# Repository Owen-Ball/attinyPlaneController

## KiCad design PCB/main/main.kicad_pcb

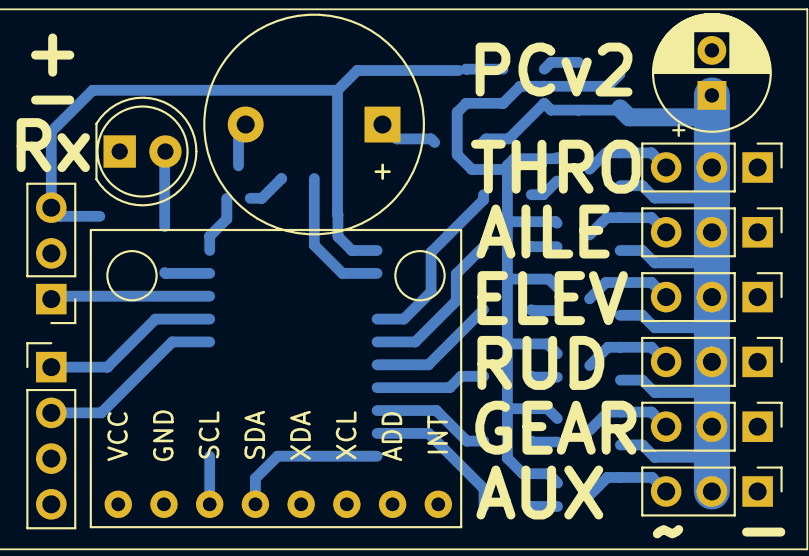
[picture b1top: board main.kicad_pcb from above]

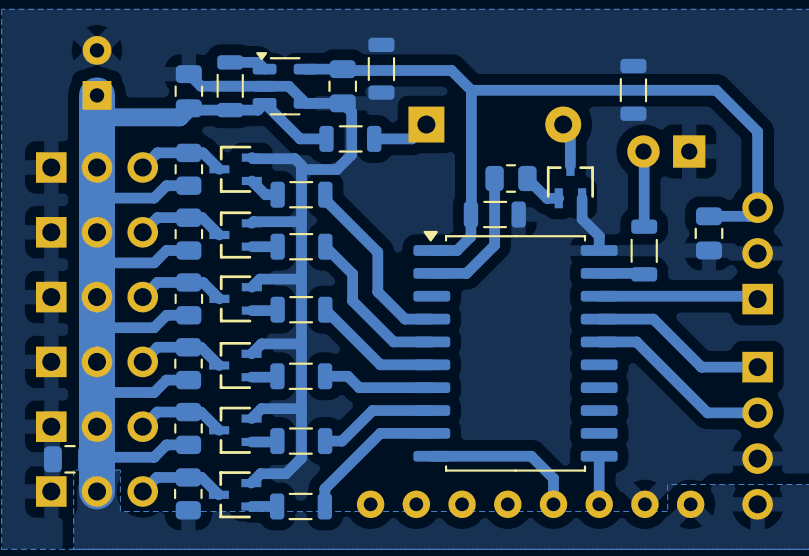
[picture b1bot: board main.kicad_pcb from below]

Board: 2 copper layers, 44 parts (32 on the bottom side), 32 nets.

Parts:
BZ1: Buzzer; Buzzer_12x9.5RM7.6
C1: C; C_0805_Long
C2, C6: 10u; C_0805_2012Metric
C3: 1u; C_0805_2012Metric
C4: 220u; CP_Radial_D6.3mm_P2.50mm
C5: C; C_0805_2012Metric
D1: LED; LED_D5.0mm
J1, J2, J3, J4, J5, J6, J8: Conn_01x03_Pin; PinHeader_1x03_P2.54mm_Vertical
J7: Conn_01x04_Pin; PinHeader_1x04_P2.54mm_Vertical
R1, R4, R6, R8, R10, R12, R13: R_US; R_0805_2012Metric
R2, R3, R5, R7, R9, R11: R_US; C_0805_Long
R14: 470; C_0805_Long
R15, R16, R17, R18: 0; C_0805_Long
U1: ATtiny3226-S; SOIC-20W_7.5x12.8mm_P1.27mm
U2: TPS7A2033PDBVR; SOT-23-5
U3, U4, U5, U6, U7, U8, U9: DMG1012UW-7; SOT_12UW-7_DIO
U10: module_mpu6050

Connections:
+3V3: C1.1, C2.1, C5.1, J8.3, U1.1 (VCC), U2.5 (OUT)
+5V: BZ1.1 (+), C3.1, C4.1, C6.1, J1.2, J2.2, J3.2, J4.2, J5.2, J6.2, J7.4, R1.1, R4.1, R6.1, R8.1, R10.1, R12.1, R15.1, R16.1, R16.2, U2.3 (EN), U10.1 (VCC)
/BUZ: R13.1, U1.2 (PA4)
/DEBUG_TX: J7.1, U1.17 (PA1)
/LED: R14.2, U1.19 (PA3)
/PWM1: J1.3, R1.2, U3.3 (D)
/PWM1_b: R2.1, U1.4 (PA6)
/PWM2: J2.3, R4.2, U4.3 (D)
/PWM2_b: R3.1, U1.5 (PA7)
/PWM3: J3.3, R6.2, U5.3 (D)
/PWM3_b: R5.1, U1.6 (PB5)
/PWM4: J4.3, R8.2, U6.3 (D)
/PWM4_b: R7.1, U1.7 (PB4)
/PWM5: J5.3, R10.2, U7.3 (D)
/PWM5_b: R9.1, U1.8 (PB3)
/PWM6: J6.3, R12.2, U8.3 (D)
/PWM6_b: R11.1, U1.9 (PB2)
/RX: J8.1, U1.18 (PA2)
/SCL: U1.11 (PB0), U10.3 (SCL)
/SDA: U1.10 (PB1), U10.4 (SDA)
/UPDI: J7.2, U1.16 (~RESET/PA0)
GND: C1.2, C2.2, C3.2, C4.2, C5.2, C6.2, D1.1 (K), J1.1, J2.1, J3.1, J4.1, J5.1, J6.1, J7.3, J8.2, R17.1, R17.2, R18.1, R18.2, U1.20 (GND), U2.2 (GND), U2.4 (NC), U3.2 (S), U4.2 (S), U5.2 (S), U6.2 (S), U7.2 (S), U8.2 (S), U9.2 (S), U10.2 (GND)
unnamed: BZ1.2 (-), U9.3 (D)
unnamed: D1.2 (A), R14.1
unnamed: R15.2, U2.1 (IN)
unnamed: R2.2, U3.1 (G)
unnamed: R3.2, U4.1 (G)
unnamed: R5.2, U5.1 (G)
unnamed: R7.2, U6.1 (G)
unnamed: R9.2, U7.1 (G)
unnamed: R11.2, U8.1 (G)
unnamed: R13.2, U9.1 (G)

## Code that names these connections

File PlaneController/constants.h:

#ifndef _CONSTANTS_
#define _CONSTANTS_

enum MODE {FAILSAFE, RATE_MODE, ANGLE_MODE, MANUAL_MODE};
enum SWITCH_MODE {ANGLE_MANUAL, RATE_MANUAL};

#define ELEV_ANGLE  25.0
#define AIL_ANGLE   25.0
#define RUD_RATE    300.0
#define MIN_THROTTLE  20 //out of 255

#define RC_MIN  153.0
#define RC_MAX  870.0

#define SSPIN PIN_PC3
#define BUZ_PIN PIN_PA4
#define BAT_PIN PIN_PB1

#define MOTOR1 PIN_PA6
#define MOTOR2 PIN_PA5
#define MOTOR3 PIN_PA3
#define MOTOR4 PIN_PB0

#define SWITCH_TIME 200000

#define IMU_ADDR  0x68

#define AX_MAX 8280
#define AX_MIN -8140

#endif

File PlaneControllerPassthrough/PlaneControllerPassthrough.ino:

#include <Arduino.h>
#include "PID.h"
#include "Buzzer.h"
#include "RC.h"
#include "IMU.h"
#include "helpers.h"
#include "Motors.h"
#include "FSM.h"
#include "Servo_inverted.h"
//#include <Servo_megaTinyCore.h>

long t;
long loop_time;
long prev_time;

//PID elev(1, .5, .175);
//PID ail(1, .5, .175);
PID elev(.8, .5, .125);
PID ail(.8, .5, .125);
PID rud(2, 0, 0);

Buzzer buzzer(BUZ_PIN);

bool armed = false;

Servo elevator_servo;
Servo aileron_servo;
Servo rudder_servo;
Servo throttle_servo;
Servo aux_servo;
Servo gear_servo;

void setup() {
  Serial1.begin(115200);
  Serial.begin(115200);

  analogReference(INTERNAL2V5);

  initRC(Serial1);
  
  initIMU();
  initFSM(buzzer);

  prev_time = micros();
  
  throttle_servo.attach(PIN_PA6);
  elevator_servo.attach(PIN_PB5);
  aileron_servo.attach(PIN_PA7);
  rudder_servo.attach(PIN_PB4);
  aux_servo.attach(PIN_PC0);
  gear_servo.attach(PIN_PB3);

  delay(3000);

  
}

float limitFloat(float val) {
  if (val > 2000.0) return 2000.0;
  if (val < 1000.0) return 1000.0;
  return val;
}

void loop() {
  t = micros();
  loop_time = t - prev_time;
  prev_time = t;
  runRC(t);
  runFSM(t);
  buzzer.runBuzzer(t);

  runIMU(loop_time);
  //Serial1.print(getThrottle());
  //Serial1.print(" ");
  //Serial1.println(getAileron());
  if (SYSTEM_MODE == FAILSAFE) {
    throttle_servo.writeMicroseconds(1000);
    elevator_servo.writeMicroseconds(1500);
    aileron_servo.writeMicroseconds(1500);
    rudder_servo.writeMicroseconds(1500);
    aux_servo.writeMicroseconds(1500);
    gear_servo.writeMicroseconds(1500);
    
  } else {
    throttle_servo.writeMicroseconds(getThrottle());
    elevator_servo.writeMicroseconds(reverseChannel(getElevator()));
    aileron_servo.writeMicroseconds(limitFloat(reverseChannel(getAileron()) - 300*getAux()));
    rudder_servo.writeMicroseconds(reverseChannel(getRudder()));
    aux_servo.writeMicroseconds(limitFloat(reverseChannel(getAileron()) + 300*getAux()));
    gear_servo.writeMicroseconds(1500);
  }
}
